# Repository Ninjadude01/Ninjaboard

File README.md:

# Ninjaboard

My project is a custom PCB controller board! How it works is that a random LED will light up, and you have to press the corresponding keyboard switch in less than one second. This will continue untill you lose, and once you do, the LED's do a fun game over sequence. I decided to make this project because I have never make a PCB controller before, and I always love trying new things. Another reason I chose this project is because I am interested in hardware, however I haven't done much of that up until I head about Stasis, so I am really glad to have gotten an oppertunity to do things that I enjoy. 

Here is what it looks like:

Here is the schematic diagram:

Here is the PCB design:

BOM:

|Item|Part Name       |Quantity|Description|Cost |Link                                                                                                                                                                                                                                                                                                                                                                                                                                                                                                                                                                                                                                                                                             |
|----|----------------|--------|-----------|-----|-------------------------------------------------------------------------------------------------------------------------------------------------------------------------------------------------------------------------------------------------------------------------------------------------------------------------------------------------------------------------------------------------------------------------------------------------------------------------------------------------------------------------------------------------------------------------------------------------------------------------------------------------------------------------------------------------|
|1   |LED             |10      |Light      |$1.17|https://www.aliexpress.com/item/32759416007.html?spm=a2g0o.productlist.main.25.5ad45d4fBpD18Y&algo_pvid=c7d3ffdf-054c-4a00-8b1f-7dc1258b8f89&algo_exp_id=c7d3ffdf-054c-4a00-8b1f-7dc1258b8f89-24&pdp_ext_f=%7B%22order%22%3A%2263%22%2C%22spu_best_type%22%3A%22price%22%2C%22eval%22%3A%221%22%2C%22fromPage%22%3A%22search%22%7D&pdp_npi=6%40dis%21CAD%212.47%211.60%21%21%211.76%211.14%21%402103110517740490152535062ebe05%2112000027866463708%21sea%21CA%217451194651%21ABX%211%210%21n_tag%3A-29910%3Bd%3A8fd05d1b%3Bm03_new_user%3A-29895%3BpisId%3A5000000197831969&curPageLogUid=rJeiEFxpdOuU&utparam-url=scene%3Asearch%7Cquery_from%3A%7Cx_object_id%3A32759416007%7C_p_origin_prod%3A|
|2   |Resistor        |100     |Resistor   |$0.73|https://www.aliexpress.com/item/1005006040209297.html?spm=a2g0o.productlist.main.1.44fe7785qfn6Bm&algo_pvid=6d8afb23-2538-424a-ae4a-d31f3bcf2f64&algo_exp_id=6d8afb23-2538-424a-ae4a-d31f3bcf2f64-0&pdp_ext_f=%7B%22order%22%3A%22341%22%2C%22spu_best_type%22%3A%22price%22%2C%22eval%22%3A%221%22%2C%22fromPage%22%3A%22search%22%7D&pdp_npi=6%40dis%21CAD%210.72%210.72%21%21%210.51%210.51%21%402101e80317740488821005309e1bc6%2112000035442807620%21sea%21CA%217451194651%21ABX%211%210%21n_tag%3A-29910%3Bd%3A8fd05d1b%3Bm03_new_user%3A-29895&curPageLogUid=NUwI7MvNd3uo&utparam-url=scene%3Asearch%7Cquery_from%3A%7Cx_object_id%3A1005006040209297%7C_p_origin_prod%3A                  |
|3   |Xiao rp 2040    |1       |PCB        |$3.59|https://www.aliexpress.com/item/1005003908237026.html?spm=a2g0o.cart.0.0.6df938dabXCDew&mp=1&pdp_npi=6%40dis%21CAD%21CAD%2011.73%21CAD%204.93%21%21CAD%204.75%21%21%21%40210328df17740487064442830e3672%2112000056511616306%21ct%21CA%217451194651%21%216%210%21                                                                                                                                                                                                                                                                                                                                                                                                                                 |
|4   |Cherry mx switch|10      |Input      |$2.60|https://www.aliexpress.com/item/1005008811335051.html?spm=a2g0o.cart.0.0.6df938dabXCDew&mp=1&pdp_npi=6%40dis%21CAD%21CAD%2052.73%21CAD%2045.79%21%21CAD%2044.15%21%21%21%40210328df17740487064442830e3672%2112000046764301536%21ct%21CA%217451194651%21%211%210%21                                                                                                                                                                                                                                                                                                                                                                                                                               |
|5   |Cherry mx Keycap|5       |Input      |$1.17|https://www.aliexpress.com/item/1005008795444732.html?spm=a2g0o.productlist.main.3.4ba1nQTEnQTEAd&algo_pvid=f2a257d6-f6ba-4a56-844c-46b02c23fcf6&algo_exp_id=f2a257d6-f6ba-4a56-844c-46b02c23fcf6-2&pdp_ext_f=%7B%22order%22%3A%22687%22%2C%22eval%22%3A%221%22%2C%22fromPage%22%3A%22search%22%7D&pdp_npi=6%40dis%21CAD%215.69%211.60%21%21%214.05%211.14%21%402101f70717740488092483736e5c9e%2112000046697462916%21sea%21CA%217451194651%21ABX%211%210%21n_tag%3A-29910%3Bd%3A8fd05d1b%3Bm03_new_user%3A-29895%3BpisId%3A5000000197831899&curPageLogUid=ol1gduKDApl2&utparam-url=scene%3Asearch%7Cquery_from%3A%7Cx_object_id%3A1005008795444732%7C_p_origin_prod%3A                           |
|6   |Custom PCB      |5       |PCB        |$1.50|https://jlcpcb.com/                                                                                                                                                                                                                                                                                                                                                                                                                                                                                                                                                                                                                                                                              |

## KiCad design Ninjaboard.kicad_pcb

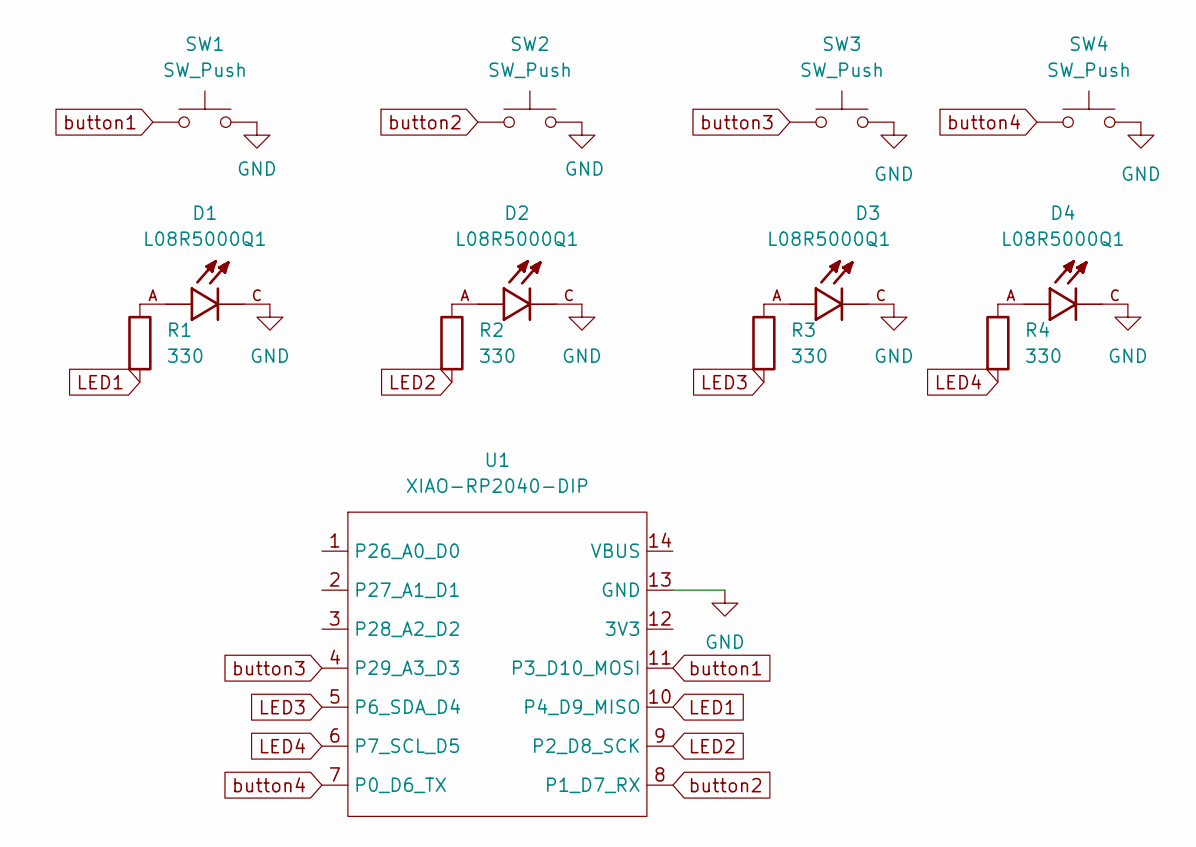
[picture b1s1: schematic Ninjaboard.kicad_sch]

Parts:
D1, D2, D3, D4: L08R5000Q1; LEDRD254W57D500H1070; PARTREV NA
R1, R2, R3, R4: 330; R_Axial_DIN0204_L3.6mm_D1.6mm_P5.08mm_Horizontal
SW1, SW2, SW3, SW4: SW_Push; SW_Cherry_MX_1.00u_PCB
U1: XIAO-RP2040-DIP

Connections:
GND: D1.C, D2.C, D3.C, D4.C, SW1.2, SW2.2, SW3.2, SW4.2, U1.13 (GND)
LED1: R1.2, U1.10 (P4_D9_MISO)
LED2: R2.2, U1.9 (P2_D8_SCK)
LED3: R3.2, U1.5 (P6_SDA_D4)
LED4: R4.2, U1.6 (P7_SCL_D5)
unnamed: D1.A, R1.1
unnamed: D2.A, R2.1
unnamed: D3.A, R3.1
unnamed: D4.A, R4.1
button1: SW1.1, U1.11 (P3_D10_MOSI)
button2: SW2.1, U1.8 (P1_D7_RX)
button3: SW3.1, U1.4 (P29_A3_D3)
button4: SW4.1, U1.7 (P0_D6_TX)

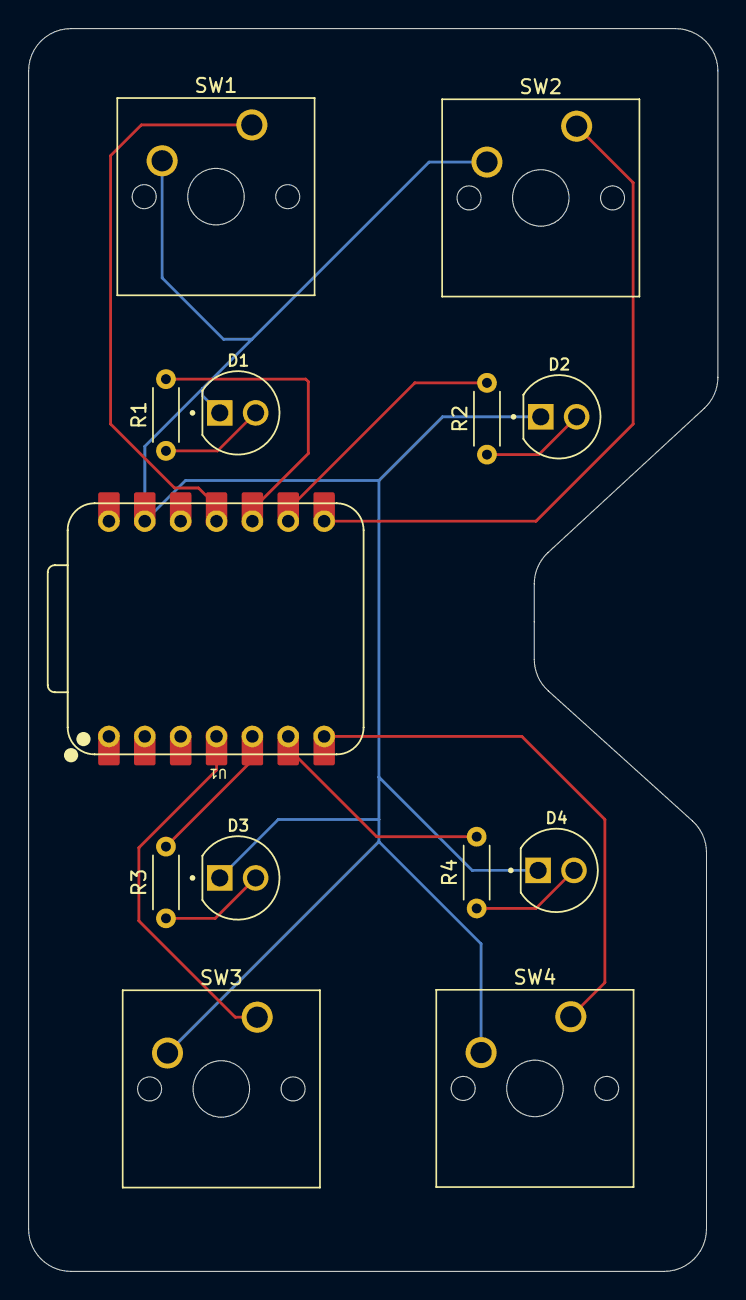
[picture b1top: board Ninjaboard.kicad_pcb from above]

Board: 2 copper layers, 48.8 x 88.0 mm, 13 parts (0 on the bottom side), 13 nets.

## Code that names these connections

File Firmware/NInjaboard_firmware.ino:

int BUT1 = D10;
int BUT2 = D7;
int BUT3 = D3;
int BUT4 = D6;

int LED1 = D9;
int LED2 = D8;
int LED3 = D4;
int LED4 = D5;

int ledPins[] = {D9, D8, D4, D5};   
int butPins[] = {D10, D7, D3, D6};

unsigned long starttime = 0;
bool pressed = false;
bool endcode = false;

void setup() {

  Serial.begin(9600);
  randomSeed(analogRead(A0));

  pinMode(BUT1, INPUT_PULLUP);
  pinMode(BUT2, INPUT_PULLUP);
  pinMode(BUT3, INPUT_PULLUP);
  pinMode(BUT4, INPUT_PULLUP);

  pinMode(LED1, OUTPUT);
  pinMode(LED2, OUTPUT);
  pinMode(LED3, OUTPUT);
  pinMode(LED4, OUTPUT);

}

void loop() {
  while(endcode == false){
    pressed = false;
    delay (500);

    int randNum = random (4);

    int currentLED = LED[randNum];
    int currentBUT = BUT[randNum];

    digitalWrite(currentLED, HIGH);
    starttime = millis();

    while(millis() - starttime < 1000){
      if(digitalRead(currentBUT) == LOW){
        pressed = true;
        digitalWrite(currentLED, LOW);
        break;}}


    if(!pressed){
      digitalWrite(currentLED, LOW);
      
      for(int c = 0; c < 3; c ++){
      digitalWrite(LED1, HIGH);
      digitalWrite(LED2, HIGH);  
      digitalWrite(LED3, HIGH);
      digitalWrite(LED4, HIGH);  
      delay (500);

      digitalWrite(LED1, LOW);
      digitalWrite(LED2, LOW);  
      digitalWrite(LED3, LOW);
      digitalWrite(LED4, LOW);  
      delay (500);}
      
      endcode = true;}
      
  }
}



   


      


  

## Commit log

2026-03-20 Create temp
2026-03-31 Rename Ninjaboard.kicad_pcb to Kicad_Source_Files/Ninjaboard.kicad_pcb
2026-03-31 Rename Ninjaboard.kicad_sch to Kicad_Source_Files/Ninjaboard.kicad_sch
2026-03-31 Rename Ninjaboard.step to 3D_Model_Files/Ninjaboard.step
